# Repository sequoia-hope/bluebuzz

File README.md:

# bluebuzz-rm2

**Live project page & interactive schematic / PCB / 3D viewer:** <https://sequoia-hope.github.io/bluebuzz/> ([full-window board viewer](https://sequoia-hope.github.io/bluebuzz/viewer/), [renders & 3D gallery](https://sequoia-hope.github.io/bluebuzz/out/index.html))

A Bluetooth vibrator controller: RP2350A + Raspberry Pi Radio Module 2
(the first board, an nRF52840 module, is abandoned and kept in
`archive/nrf52840/`):
Wi-Fi 4 and Bluetooth 5.2 Classic + LE (CYW43439), so the toy can be a
Bluetooth **A2DP audio sink** (BTstack, in the Pico SDK) as well as a
BLE-controlled device, and a **USB audio device** (TinyUSB) over its USB-C.
**26 × 56.84 mm (`squish_pcb.dxf` with r = 10 mm lower tip offset inward by 2.0 mm), 6 layers.**
USB-C on the bottom tip is the only connector (the top dome is the RM2's RF keep-out);
every other lead is an SMT pad row on the back.

Sensing is a **4-sensor diamond array of Infineon DPS368 barometers on the back**
(North, East, West, South), meant to be cast in soft elastomer after Tenzer, Jentoft
& Howe, *The Feel of MEMS Barometers* (IEEE RAM 2014): rubber poured over
the array and vacuum degassed so it fills the pressure ports, after which
a load on the surface reads as pressure, linear to under 1 %, with 10 mN
resolution. Each sensor is on SPI1 with its own chip select (CSB low at
power-up selects SPI; the part has only two I2C addresses), on the
switched 3.3 V rail, 100n beside it. An **MP34DT05TR-A top-port digital PDM MEMS microphone** (`U40`) sits on the front upper-right shoulder (`PDM_CLK` on GPIO29, `PDM_DATA` on GPIO28), and an
**LSM6DS3TR-C IMU** on I2C1 sits on the back on the always-on rail,
with both interrupts on GPIOs for wake-on-motion.

Same pipeline as the parent (`python3 build.py` here; the `site` stage
rebuilds board `b` of the parent's `pcbview.toml`), with additions this
denser board forced: `route.py` hands freerouting a tamed DSN (GND
removed from its netlist since planes and pours carry it, the plane
layers marked unroutable, its fixed GND copper turned into keepouts),
lays the nets freerouting never closed by hand (the six QSPI lines, VBAT,
PG_N, the PWM and SWD hops, the USB climb, LX, WL_CS, the RP2350's lone
GND pin), draws every hand-laid bend at 45 degrees, and after routing
puts a via in every GND pad it can (cutting freerouting's wires from
under the ones it walled off; the finish stage re-closes them). The
stackup is six layers (GND / signal / VSYS pour / GND inside) because
four left 40-55 connections open. `ROUTE_DRY=1 python3 scripts/route.py`
lays only the locked pre-routes, for a quick DRC of them.

## What it is

| | |
|---|---|
| Host | RP2350A (QFN-60), Raspberry Pi's minimal design: 3.3 µH core buck, 12 MHz crystal (12 pF CL, 18 pF loads), W25Q32JVUUIQ 32 Mbit QSPI flash (3 x 4 USON), 27 R USB series, 10k/100n on RUN |
| Radio | RM2 (RMC20452T): gSPI with CS 25 as the Pico W, WL_ON on GPIO27, DATA on GPIO2 and CLK on GPIO3 (the board header overrides the SDK's defaults), DOUT via 470 R and nIRQ via 10 k into DATA. Vin from **VSYS** (3.0–4.8 V), VDDIO 3.3 V. Antenna end at the top board edge; the datasheet's RF keep-out is the top 5 mm of the board on every layer |
| Power | BQ24074 charger with power path (VBUS from the USB-C), TLV75533 3.3 V, TPS22918 switched sensor rail (GPIO4). /PGOOD → GPIO9 (the RP2350 has no VBUS detect) |
| Motors | two AO3400A low-side channels (GPIO13, GPIO17), 100 R gate / 100k pull-down, B5819W flybacks, 2 x 22 µF; pads VSYS M1 M2; 1 A per channel, fine for 3.7 V vibration motors |
| Touch | 4 x DPS368 on the back (SPI1: GPIO10 SCK, 11 SDI, 12 SDO; CS GPIO13-16), switched rail |
| Motion | LSM6DS3TR-C on I2C1 (GPIO6/7, 4.7k pull-ups), INT1/INT2 on GPIO5/18, CS high (I2C), SA0 low (0x6A), always on |
| UI | side button GPIO8, status LED GPIO22, charge LED on /CHG; battery 1M/1M into ADC0 = GPIO26 |
| USB | USB-C receptacle on the bottom edge, 5.1k on each CC, USBLC6-2P6 ESD, 27 R series at the chip |
| Pads (back, 1.6 x 2.2 mm at 2.0 mm) | top: **BAT** + - · bottom-left: **MOT** VSYS M1 M2 · under the radio: **SWD** SWDIO SWCLK RUN BOOT GND (pogo) |

## Programming

Bridge the **BOOT** pad to the **GND** pad beside it while applying
power (or call `reset_usb_boot()` from firmware) and the RP2350
enumerates as a UF2 drive on the USB-C. SWD on the same pad row for
debugging. Firmware: Pico SDK with `PICO_CYW43_SUPPORTED` and a board file
setting `CYW43_DEFAULT_PIN_WL_DATA_OUT/_IN/_HOST_WAKE = 2` and
`CYW43_DEFAULT_PIN_WL_CLOCK = 3`; BTstack's A2DP sink example is the
starting point for sound-to-vibration; the DPS368s through `spi1`, one
chip select at a time, in background mode at the rate the elastomer
response needs (the paper sampled at 100 Hz per sensor).

## Casting the array

Per the paper: a two-part room-temperature polyurethane (they used
VytaFlex 20, E ≈ 280 kPa) poured over the back of the board to 4-10 mm
over the sensors, then the mould placed in a vacuum chamber immediately
so the air trapped in the sensor ports is pulled out and the rubber
fills them; thinner rubber is more sensitive (1380 counts/N at 4 mm vs
165 at 10 mm for their sensor), thicker spreads the response. Solder the
BAT and MOT leads before casting; the SWD pads under the radio can stay
outside the cast area.

## Before ordering

- The **RM2 is not an LCSC part**: Raspberry Pi approved resellers; consign
  it at JLCPCB or solder it by hand (castellated, 1.5 mm pitch).
- The RM2 footprint was drawn from the datasheet's figure 6 (release 7,
  2026-02, `docs/RM2-datasheet.pdf`); check it against a module in hand.
- The DPS368 footprint is the LCSC/EasyEDA land for C3232508 (two
  columns of four 0.6 x 0.4 mm pads, 0.65 mm pitch, 1.45 mm apart);
  check it against Infineon's drawing. Pin 1 is the top-right pad.
- The DPS368 and the LSM6DS3TR-C are JLCPCB "extended" parts (a loading
  fee each per order). DPS368: $4.21 at 1-9, $3.60 at 10+ (2026-10).
- The flash is the 3 x 4 mm W25Q32JVUUIQ because the 2 x 3 mm 16 Mbit
  part had no stock; its KiCad land is by package name, check it against
  Winbond's drawing.
- No 3D models for the RM2 (not on LCSC) and the core inductor (LCSC
  land differs from KiCad's); the viewer draws boxes for them.

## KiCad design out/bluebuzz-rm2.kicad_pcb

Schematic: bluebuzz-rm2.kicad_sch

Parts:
C2, C13, C14, C15, C41, C43, C64, C82, C88, C89, C91, C92, C93, C94, C95, C96, C97, C98, C101, C102, C120, C121, C122, C123, C130, C132, C133, C140: 100n; C_0402_1005Metric
C10, C11, C12, C22, C52, C100, C131: 10u; C_0603_1608Metric
C20, C21, C51, C85: 1u; C_0603_1608Metric
C40, C42: 22u; C_0603_1608Metric
C50: 470p; C_0402_1005Metric
C80, C83: 4.7u; C_0402_1005Metric_small_pads
C81, C84: 4.7u; C_0402_1005Metric
C86, C87: 15p; C_0402_1005Metric
D1: CHG; LED_0603_1608Metric
D2: XL-1010RGBC; LED_1010_WS2812
D3, D4: B5819W; D_SOD-123
D5: BAT54C; SOT-23
D6: 1N4148WS; D_SOD-323
J1: USB-C; USB_C_Receptacle_HRO_TYPE-C-31-M-12
J2: BAT; PadRow_3x_solder
J3: SWD; PadRow_5x_pogo
J4: MOT; PadRow_3x_solder
J5: TP; PadRow_3x_pogo
J6: PROBE; JST_SH_BM03B-SRSS-TB_1x03-1MP_P1.00mm_Vertical; not fitted
L1: 3.3u; L_pol_2016
Q1, Q2: AO3400A; SOT-23
Q3: 2N7002; SOT-23
R1, R2: 5.1k; R_0402_1005Metric
R3, R4: 27R; R_0402_1005Metric
R10: 1.78k; R_0402_1005Metric
R11: 1.62k; R_0402_1005Metric
R12: 45.3k; R_0402_1005Metric
R13, R81, R88: 10k; R_0402_1005Metric
R14, R62: 330R; R_0402_1005Metric
R40, R42: 100R; R_0402_1005Metric
R41, R43, R130, R131: 4.7k; R_0402_1005Metric
R50, R63, R64, R66: 100k; R_0402_1005Metric
R60, R61: 1M; R_0402_1005Metric
R80: 470R; R_0402_1005Metric
R84: 33R; R_0402_1005Metric
R85: 10R; R_0402_1005Metric
R86, R87: 1k; R_0402_1005Metric
SW1: PWR; Panasonic_EVQPUL_EVQPUC
U1: RP2350A; QFN-60-1EP_7x7mm_P0.4mm_EP3.4x3.4mm_ThermalVias
U2: BQ24074RGT; VQFN-16-1EP_3x3mm_P0.5mm_EP1.6x1.6mm
U3: TLV75533PDBV; SOT-23-5
U5, U11: TPS22918DBVR; SOT-23-6
U6: W25Q32JVUUIQ; Winbond_USON-8-2EP_3x4mm_P0.8mm_EP0.2x0.8mm
U7: RM2
U10: USBLC6-2P6; SOT-666
U20, U21, U22, U23: DPS368; DPS368_LGA-8
U30: LSM6DS3TR-C; LGA-14_3x2.5mm_P0.5mm_LayoutBorder3x4y
U40: MP34DT05-A; MP34DT05_HCLGA-4
Y1: 12MHz; Crystal_SMD_3225-4Pin_3.2x2.5mm

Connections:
1V1: C80.1, C81.1, C82.1, C98.1, J5.3 (1V1), L1.1, U1.6 (DVDD), U1.23 (DVDD), U1.39 (DVDD), U1.50 (VREG_FB)
3V3A: C85.1, R85.2, U1.44 (ADC_AVDD)
3V3_SENS: C52.1, C120.1, C121.1, C122.1, C123.1, U5.5 (QOD), U5.6 (VOUT), U20.6 (VDDIO), U20.8 (VDD), U21.6 (VDDIO), U21.8 (VDD), U22.6 (VDDIO), U22.8 (VDD), U23.6 (VDDIO), U23.8 (VDD)
3V3_SYS: C21.1, C22.1, C51.1, C83.1, C88.1, C91.1, C92.1, C93.1, C94.1, C95.1, C96.1, C97.1, C102.1, C130.1, C131.1, C132.1, C140.1, J5.2 (3V3), R84.1, R85.1, R88.1, R130.1, R131.1, U1.1 (IOVDD), U1.11 (IOVDD), U1.20 (IOVDD), U1.30 (IOVDD), U1.38 (IOVDD), U1.45 (IOVDD), U1.49 (VREG_VIN), U1.53 (USB_OTP_VDD), U1.54 (IOVDD), U3.5 (OUT), U5.1 (VIN), U6.8 (VCC), U7.14 (VDDIO), U11.3 (ON), U30.5 (VDDIO), U30.8 (VDD), U30.12 (CS), U40.1 (VDD)
BOOTSEL: J3.4 (BOOT), R87.2
BTN: Q3.3 (D), U1.12 (GPIO8/BTN)
BTN_RAW: D5.1 (A1), Q3.1 (G), R64.1, SW1.2
CC1: J1.A5 (CC1), R1.1
CC2: J1.B5 (CC2), R2.1
CHG_LED: D1.1 (K), R14.1
CHG_N: R14.2, U2.9 (/CHG)
CT_SENS: C50.1, U5.4 (CT)
GND: C2.2, C10.2, C11.2, C12.2, C13.2, C14.2, C15.2, C20.2, C21.2, C22.2, C40.2, C41.2, C42.2, C43.2, C50.2, C51.2, C52.2, C64.2, C80.2, C81.2, C82.2, C83.2, C84.2, C85.2, C86.2, C87.2, C88.2, C89.2, C91.2, C92.2, C93.2, C94.2, C95.2, C96.2, C97.2, C98.2, C100.2, C101.2, C102.2, C120.2, C121.2, C122.2, C123.2, C130.2, C131.2, C132.2, C133.2, C140.2, D2.3 (GND), J1.A1 (GND), J1.A12 (GND), J1.B1 (GND), J1.B12 (GND), J1.S1 (SHIELD), J2.2 (-), J3.5 (GND), J6.2 (GND), J6.MP, Q1.2 (S), Q2.2 (S), Q3.2 (S), R1.2, R2.2, R10.2, R11.2, R12.2, R13.2, R41.2, R43.2, R50.2, R61.2, R63.2, R64.2, U1.47 (GND), U1.61 (GND), U2.4 (/CE), U2.6 (EN1), U2.8 (VSS), U2.17 (VSS), U3.2 (GND), U5.2 (GND), U6.4 (GND), U7.1 (GND), U7.4 (GND), U7.7 (GND), U7.11 (GND), U7.15 (GND), U7.21 (GND), U10.2 (GND), U11.2 (GND), U20.1 (GND), U20.7 (GND), U21.1 (GND), U21.7 (GND), U22.1 (GND), U22.7 (GND), U23.1 (GND), U23.7 (GND), U30.1 (SA0), U30.2 (SDx), U30.3 (SCx), U30.6 (GND), U30.7 (GND), U40.2 (LR), U40.5 (GND), Y1.2, Y1.4
ILIM: R11.1, U2.12 (ILIM)
IMU_INT1: U1.8 (GPIO5/IMU_INT1), U30.4 (INT1)
IMU_INT2: U1.29 (GPIO18/IMU_INT2), U30.9 (INT2)
ISET: R10.1, U2.16 (ISET)
LDO_EN: D5.3 (K), R63.1, R66.2, U3.3 (EN)
LED_DIN: D2.4 (DI), R62.2
LED_STAT: R62.1, U1.34 (GPIO22/LED)
LED_VDD: C133.1, D2.2 (VDD), U11.5 (QOD), U11.6 (VOUT)
MOTOR1_G: Q1.1 (G), R40.2, R41.1
MOTOR1_PWM: R40.1, U1.17 (GPIO13/M1_PWM)
MOTOR1_SW: D3.2 (A), J4.2 (M1), Q1.3 (D)
MOTOR2_G: Q2.1 (G), R42.2, R43.1
MOTOR2_PWM: R42.1, U1.28 (GPIO17/M2_PWM)
MOTOR2_SW: D4.2 (A), J4.3 (M2), Q2.3 (D)
PDM_CLK: U1.43 (GPIO29/PDM_CLK), U40.3 (CLK)
PDM_DATA: U1.42 (GPIO28/PDM_DATA), U40.4 (DOUT)
PG_N: U1.13 (GPIO9/PG), U2.7 (/PGOOD)
PWR_HOLD: D5.2 (A2), U1.31 (GPIO19/PWR_HOLD)
QSPI_SCLK: U1.56 (QSPI_SCLK), U6.6 (CLK)
QSPI_SD0: U1.57 (QSPI_SD0), U6.5 (DI/IO0)
QSPI_SD1: U1.59 (QSPI_SD1), U6.2 (DO/IO1)
QSPI_SD2: U1.58 (QSPI_SD2), U6.3 (/WP/IO2)
QSPI_SD3: U1.55 (QSPI_SD3), U6.7 (/HOLD/IO3)
QSPI_SS: R87.1, U1.60 (QSPI_SS), U6.1 (/CS)
RUN: C89.1, J3.3 (RUN), R88.2, U1.26 (RUN)
SCL: R131.2, U1.10 (GPIO7/SCL), U30.13 (SCL)
SDA: R130.2, U1.9 (GPIO6/SDA), U30.14 (SDA)
SENS_EN: R50.1, U1.7 (GPIO4/SENS_EN), U5.3 (ON)
SWCLK: J3.2 (SWCLK), J6.1 (SC), U1.24 (SWCLK)
SWDIO: J3.1 (SWDIO), J6.3 (SD), U1.25 (SWDIO)
TAC_CS1: U1.2 (GPIO0/TAC_CS1), U20.2 (CSB)
TAC_CS2: U1.18 (GPIO14/TAC_CS2), U21.2 (CSB)
TAC_CS3: U1.19 (GPIO15/TAC_CS3), U22.2 (CSB)
TAC_CS4: U1.27 (GPIO16/TAC_CS4), U23.2 (CSB)
TAC_SCK: U1.14 (GPIO10/TAC_SCK), U20.4 (SCK), U21.4 (SCK), U22.4 (SCK), U23.4 (SCK)
TAC_SDI: U1.15 (GPIO11/TAC_SDI), U20.3 (SDI), U21.3 (SDI), U22.3 (SDI), U23.3 (SDI)
TAC_SDO: U1.16 (GPIO12/TAC_SDO), U20.5 (SDO), U21.5 (SDO), U22.5 (SDO), U23.5 (SDO)
TMR: R12.1, U2.14 (TMR)
TS: J2.3 (T), R13.1, U2.1 (TS)
USB_DM: J1.A7 (D-), J1.B7 (D-), R4.1, U10.3 (IO2), U10.4 (IO2)
USB_DM_C: R4.2, U1.51 (USB_DM)
USB_DP: J1.A6 (D+), J1.B6 (D+), R3.1, U10.1 (IO1), U10.6 (IO1)
USB_DP_C: R3.2, U1.52 (USB_DP)
VBAT: C12.1, C15.1, J2.1 (+), R60.1, U2.2 (BAT), U2.3 (BAT)
VBAT_SENSE: C64.1, R60.2, R61.1, U1.40 (GPIO26/ADC0)
VBUS: C2.1, C10.1, C13.1, D6.2 (A), J1.A4 (VBUS), J1.A9 (VBUS), J1.B4 (VBUS), J1.B9 (VBUS), U2.13 (IN), U10.5 (VBUS)
VBUS_EN: D6.1 (K), R66.1
VREG_AVDD: C84.1, R84.2, U1.46 (VREG_AVDD)
VREG_LX: L1.2, U1.48 (VREG_LX)
VSYS: C11.1, C14.1, C20.1, C40.1, C41.1, C42.1, C43.1, C100.1, C101.1, D1.2 (A), D3.1 (K), D4.1 (K), J4.1 (VSYS), J5.1 (VSYS), SW1.1, U2.5 (EN2), U2.10 (OUT), U2.11 (OUT), U3.1 (IN), U7.16 (Vin), U11.1 (VIN)
WL_CLK: U1.5 (GPIO3/WL_CLK), U7.3 (SCLK)
WL_CS: U1.37 (GPIO25/WL_CS), U7.9 (CS)
WL_DATA: R80.2, R81.2, U1.4 (GPIO2/WL_DATA), U7.5 (DIN)
WL_DOUT: R80.1, U7.6 (DOUT)
WL_IRQ: R81.1, U7.10 (nIRQ)
WL_ON: U1.41 (GPIO27/WL_ON), U7.12 (WL_ON), U7.13 (WL_ON)
XIN: C86.1, U1.21 (XIN), Y1.1
XOUT: R86.1, U1.22 (XOUT)
XTAL2: C87.1, R86.2, Y1.3

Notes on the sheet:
bluebuzz-rm2 — generated schematic
109 components / 72 nets / 6-layer. Bluetooth-audio vibrator controller: RP2350A + Raspberry Pi RM2 (CYW43439); USB-C, every other lead on back-side pads; BQ24074 charger with power path, a soft power latch (button, GPIO hold, USB), two low-side motor channels, 4 DPS368 barometers on the back (four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
The one connector on the board, on the BOTTOM edge (the top edge is the
RM2's RF keep-out). A6/B6 and A7/B7 are tied or the board enumerates in
one cable orientation only; 5.1k on each CC. The USBLC6-2P6 clamps VBUS
and protects D+/D-; 27 R in each line at the RP2350 is the reference
design's.
1 — USB-C and ESD
EN2 = 1, EN1 = 0: the R_ILIM input limit (0.99 A). 45.3k = 6 h safety timer. ITERM open = 10% default. VSYS
is the power-path output and feeds the LDO, both motors AND the RM2 (Vin 3.0-4.8 V). /PGOOD goes to GPIO9:
the RP2350 has no VBUS detect of its own. J2: solder pads on the back for the cell: + - T. T is TS for a
cell with a 10 k NTC; fit it and leave R13 off. Without an NTC R13 holds TS mid-window (always charging).
2 — BQ24074 charger with power path
500 mA, 25 uA Iq. Feeds the RP2350, the flash, the sensors, the IMU
and the RM2's VDDIO; off (EN low) is the system's off state. The
motors and the RM2's Vin take VSYS directly.
4 — 3.3 V LDO, enabled by the power latch
1M/1M, 2.1 uA, into ADC0 (GPIO26). C64 feeds the ADC's
sampling charge; the RP2350's ADC input is 500 ohm-ish during
a sample, so oversample.
3 — battery voltage sense
Five 1.6 x 2.2 mm ENIG pads at 2.0 mm pitch for a
pogo clip: SWDIO SWCLK RUN BOOT GND. Bridge BOOT
to GND while applying power for the UF2
bootloader; SWD is for debugging only. J5: three
test pads (VSYS, 3V3, 1V1) for bring-up, GND on
the SWD row. J6: the Raspberry Pi Debug Probe's
3-pin JST-SH (1 SC, 2 GND, 3 SD), footprint only
(DNP), on the back.
6 — SWD / boot pads, test pads, debug-probe connector (back)
Press SW1: VSYS reaches the LDO's EN through D5 and 3V3 comes up; the
RP2350 boots and drives PWR_HOLD (GPIO19) high, so the board stays on
after release. Firmware reads the button on GPIO8 (Q3, active low,
internal pull-up) and switches off by driving PWR_HOLD low. R63 holds
EN off; R64 discharges the gate. USB in (VBUS through D6 and R66) also
holds EN on, so flashing and SWD need no button. Charging runs while
off. Status: a 1010 addressable RGB LED (WS2812B type) on GPIO22
through 330 R; its VSYS supply goes through U11 (a second TPS22918, ON
= 3V3_SYS), so it draws nothing while the system is off.
7 — power button (soft latch) and status LED

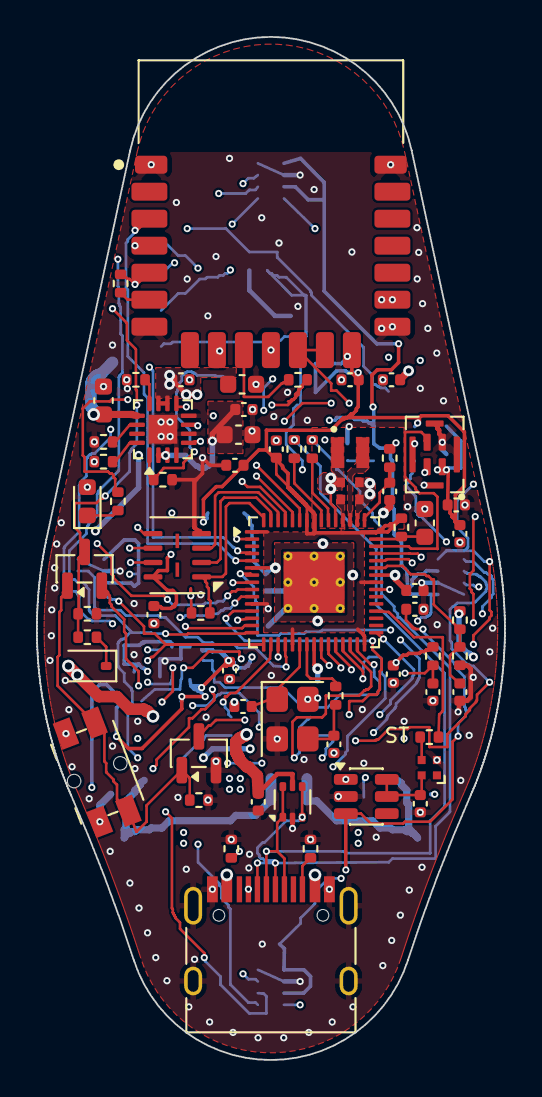
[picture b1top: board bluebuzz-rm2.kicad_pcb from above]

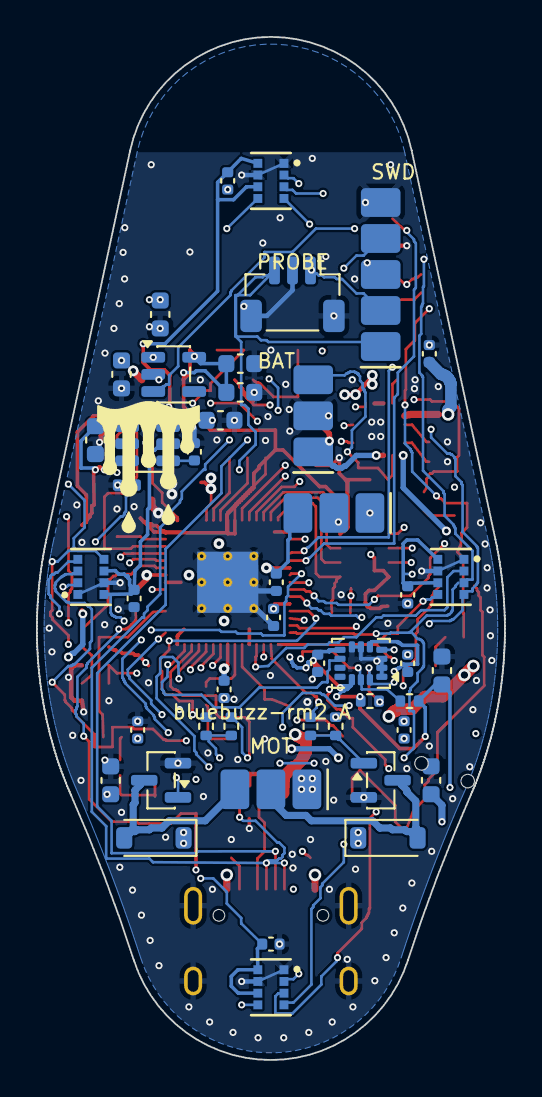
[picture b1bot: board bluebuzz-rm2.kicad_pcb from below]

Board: 6 copper layers, 26.0 x 56.8 mm, 109 parts (45 on the bottom side), 72 nets.

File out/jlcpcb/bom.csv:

Comment,Designator,Footprint,MPN,LCSC Part #
10u,"C10,C100,C11,C12,C131,C22,C52",C_0603_1608Metric,CL10A106KP8NNNC,C19702
100n,"C101,C102,C120,C121,C122,C123,C13,C130,C132,C133,C14,C140,C15,C2,C41,C43,C64,C82,C88,C89,C91,C92,C93,C94,C95,C96,C97,C98",C_0402_1005Metric,CL05B104KO5NNNC,C1525
22u,"C40,C42",C_0603_1608Metric,CL10A226MP8NUNE,C86295
470p,C50,C_0402_1005Metric,0402CG471J500NT,C75274
4.7u,"C80,C83",C_0402_1005Metric_small_pads,CL05A475MP5NRNC,C23733
4.7u,"C81,C84",C_0402_1005Metric,CL05A475MP5NRNC,C23733
1u,"C20,C21,C51,C85",C_0603_1608Metric,CL10A105KB8NNNC,C15849
15p,"C86,C87",C_0402_1005Metric,0402CG150J500NT,C1548
CHG,D1,LED_0603_1608Metric,19-217/GHC-YR1S2/6T,C2986059
XL-1010RGBC,D2,LED_1010_WS2812,XL-1010RGBC-2812B-S,C51900942
B5819W,"D3,D4",D_SOD-123,B5819W,C8598
BAT54C,D5,SOT-23,"BAT54C,215",C37704
1N4148WS,D6,D_SOD-323,1N4148WS,C2128
USB-C,J1,USB_C_Receptacle_HRO_TYPE-C-31-M-12,TYPE-C-31-M-12,C165948
3.3u,L1,L_pol_2016,AOTA-B201610S3R3-101-T,C42411119
AO3400A,"Q1,Q2",SOT-23,AO3400A,C20917
2N7002,Q3,SOT-23,2N7002,C8545
1.78k,R10,R_0402_1005Metric,0402WGF1781TCE,C113478
1.62k,R11,R_0402_1005Metric,0402WGF1621TCE,C61897
45.3k,R12,R_0402_1005Metric,0402WGF4532TCE,C26980
10k,"R13,R81,R88",R_0402_1005Metric,0402WGF1002TCE,C25744
330R,"R14,R62",R_0402_1005Metric,0402WGF3300TCE,C25104
5.1k,"R1,R2",R_0402_1005Metric,0402WGF5101TCE,C25905
27R,"R3,R4",R_0402_1005Metric,0402WGF270JTCE,C25100
100R,"R40,R42",R_0402_1005Metric,0402WGF1000TCE,C25076
4.7k,"R130,R131,R41,R43",R_0402_1005Metric,0402WGF4701TCE,C25900
1M,"R60,R61",R_0402_1005Metric,0402WGF1004TCE,C26083
100k,"R50,R63,R64,R66",R_0402_1005Metric,0402WGF1003TCE,C25741
470R,R80,R_0402_1005Metric,0402WGF4700TCE,C25117
33R,R84,R_0402_1005Metric,0402WGF330JTCE,C25105
10R,R85,R_0402_1005Metric,0402WGF100JTCE,C25077
1k,"R86,R87",R_0402_1005Metric,0402WGF1001TCE,C11702
PWR,SW1,Panasonic_EVQPUL_EVQPUC,EVQPUC02K,C79174
RP2350A,U1,QFN-60-1EP_7x7mm_P0.4mm_EP3.4x3.4mm_ThermalVias,RP2350A,C42411118
USBLC6-2P6,U10,SOT-666,USBLC6-2P6,C15999
TPS22918DBVR,"U11,U5",SOT-23-6,TPS22918DBVR,C131941
BQ24074RGT,U2,VQFN-16-1EP_3x3mm_P0.5mm_EP1.6x1.6mm,BQ24074RGTR,C54313
DPS368,"U20,U21,U22,U23",DPS368_LGA-8,DPS368XTSA1,C3232508
TLV75533PDBV,U3,SOT-23-5,TLV75533PDBVR,C404027
LSM6DS3TR-C,U30,LGA-14_3x2.5mm_P0.5mm_LayoutBorder3x4y,LSM6DS3TR-C,C967633
MP34DT05-A,U40,MP34DT05_HCLGA-4,MP34DT05TR-A,C2688664
W25Q32JVUUIQ,U6,Winbond_USON-8-2EP_3x4mm_P0.8mm_EP0.2x0.8mm,W25Q32JVUUIQ,C2999380
12MHz,Y1,Crystal_SMD_3225-4Pin_3.2x2.5mm,ABM8-272-T3,C20625731

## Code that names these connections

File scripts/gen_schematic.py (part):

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        R = list(sides.get("r", []))
        T = list(sides.get("t", []))
        B = list(sides.get("b", []))
        # Top/bottom pin names run vertically INSIDE the box and would be
        # written straight through any side-pin name whose text reaches the
        # same columns. Where they would collide, reserve as many side slots
        # as the vertical name is tall so the two never share a row.
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            ys = [p[1] for p in pts]
            if max(ys) - min(ys) >= max(xs) - min(xs):
                # pins stack vertically -> park the text alongside the body,
                # between the two pins so it cannot reach either run
                rx, ry, rj = x + hw + 0.6, y - 2.0, "left bottom"
                vx, vy, vj = x + hw + 0.6, y + 1.1, "left bottom"
            else:
                # pins run left-right -> stack the text above and below,
                # stepped off the pin axis so it clears the wires' corners
                rx, ry, rj = x + 1.9, y - hh - 2.8, "left bottom"
                vx, vy, vj = x + 1.9, y + hh + 4.2, "left bottom"
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    def label(self, net, p, rot=0, just="left", size=1.0, flag=2.54, keep=False):
        """Name a wire that KiCad would otherwise auto-name.

        These are GLOBAL labels even though the run is local, because a
        plain label on the root sheet comes back out of the netlister as
        `/LED_D7`, and the board is matched to circuit.py by net name — a
        rename would relabel every net on a hand-routed board. Drawn small
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            ("48", "VREG_LX"), None, None, None, None,
            ("46", "VREG_AVDD"), None, None, None, None, ("44", "ADC_AVDD")]
    right = [gpio(13, "M1_PWM"), gpio(17, "M2_PWM"), None,
             gpio(2, "WL_DATA"), gpio(3, "WL_CLK"), gpio(27, "WL_ON"), gpio(25, "WL_CS"), None,
             gpio(10, "TAC_SCK"), gpio(11, "TAC_SDI"), gpio(12, "TAC_SDO"), None,
             gpio(0, "TAC_CS1"), gpio(14, "TAC_CS2"), gpio(15, "TAC_CS3"), gpio(16, "TAC_CS4"), None,
             gpio(29, "PDM_CLK"), gpio(28, "PDM_DATA"), None,
             gpio(6, "SDA"), gpio(7, "SCL"), gpio(5, "IMU_INT1"), gpio(18, "IMU_INT2"), None,
             gpio(19, "PWR_HOLD"),
             gpio(4, "SENS_EN"), gpio(22, "LED"), gpio(8, "BTN"), gpio(9, "PG"), None,
             gpio(26, "ADC0")]
    top = [("1", "IOVDD", ["11", "20", "30", "38", "45", "54"]), ("49", "VREG_VIN"),
           ("53", "USB_OTP_VDD"), None, ("6", "DVDD", ["23", "39"]), ("50", "VREG_FB")]
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    "radio": {"l": [("3", "SCLK"), None, ("5", "DIN"), None, None, None, ("6", "DOUT"),
                    None, None, None, ("10", "nIRQ"), None, None, None, ("9", "CS"), None,
                    ("12", "WL_ON", ["13"])],
              "r": [("8", "GPIO0"), ("18", "GPIO1"), ("17", "GPIO2"), None,
                    ("2", "NC"), ("19", "NC"), ("20", "NC")],
              "t": [("16", "Vin"), None, None, ("14", "VDDIO")],
              "b": [("1", "GND", ["4", "7", "11", "15", "21"])]},
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    s.rail("VBUS", (u["13"][0] - 7.62, u["13"][1]))
    # /CE and EN1 to ground, EN2 to VSYS (ILIM mode, also while the system is off):
    # a short stub left, then a symbol standing the right way up
    for pin, rail, dx in (("4", "GND", 7.62), ("5", "VSYS", 15.24), ("6", "GND", 7.62)):
        bk.take("U2", pin, rail)
        e = (u[pin][0] - dx, u[pin][1])
        s.wire(u[pin], e)
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    s.rail("VBAT", (xb, u["2"][1] - 8.89))
    bk.take("U2", "7", "PG_N")
    s.wire(u["7"], (u["7"][0] + 10.16, u["7"][1]))
    s.glabel("PG_N", (u["7"][0] + 10.16, u["7"][1]))
    bk.take("U2", "9", "CHG_N")
    ych = u["9"][1]
    xled = u["9"][0] + 33.02
    s.wire(u["9"], (xled, ych))
    s.label("CHG_N", (u["9"][0] + 5.08, ych), size=1.0)
    r14 = put(s, cir, "R14", xled, ych - 3.81)
    bk.take("R14", "2", "CHG_N")
    bk.take("R14", "1", "CHG_LED")
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    bk.take("D1", "1", "CHG_LED")
    bk.take("D1", "2", "VSYS")
    s.wire(r14["1"], d1["1"])
    s.label("CHG_LED", (xled, q((r14["1"][1] + d1["1"][1]) / 2.0)), size=1.0)
    s.wire(d1["2"], (d1["2"][0], d1["2"][1] - 3.81))
    s.rail("VSYS", (d1["2"][0], d1["2"][1] - 3.81))
    ybot = u["16"][1]
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    s.note("EN2 = 1, EN1 = 0: the R_ILIM input limit (0.99 A). 45.3k = 6 h "
           "safety timer. ITERM open = 10% default. VSYS is the power-path "
           "output and feeds the LDO, both motors AND the RM2 (Vin 3.0-4.8 V). "
           "/PGOOD goes to GPIO9: the RP2350 has no VBUS detect of its own. "
           "J2: solder pads on the back for the cell: + - T. T is TS for a "
           "cell with a 10 k NTC; fit it and leave R13 off. Without an NTC "
           "R13 holds TS mid-window (always charging).",
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    s.wire((xin, u["1"][1]), (xin, u["1"][1] - 6.35))
    s.rail("VSYS", (xin, u["1"][1] - 6.35))
    s.wire(u["3"], (u["3"][0] - 17.78, u["3"][1]))
    s.glabel("LDO_EN", (u["3"][0] - 17.78, u["3"][1]), just="right")
    bk.take("U3", "5", "3V3_SYS")
    s.wire(u["5"], (u["5"][0] + 10.16, u["5"][1]))
    s.wire((u["5"][0] + 10.16, u["5"][1]), (u["5"][0] + 10.16, u["5"][1] - 6.35))
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    bk.take("C64", "1", "VBAT_SENSE")
    s.junction((x + 12.7, ymid))
    s.wire((x + 12.7, ymid), (x + 25.4, ymid))
    s.glabel("VBAT_SENSE", (x + 25.4, ymid))
    s.note("1M/1M, 2.1 uA, into ADC0 (GPIO26). C64 feeds the ADC's sampling "
           "charge; the RP2350's ADC input is 500 ohm-ish during a sample, so "
           "oversample.", x - 8.0, r61["2"][1] + 12.7, 96.0)
    s.end()
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    m1 = motor_channel(s, cir, bk, 1, x, y + 20.32)
    m2 = motor_channel(s, cir, bk, 2, x, y + 60.96)
    # pads_3: pin 2 (M1) is the middle slot of five, so the box centres on
    # channel 1's drain run; pin 3 (M2) is two rows below it
    j4 = put(s, cir, "J4", m1[0] + 40.64, m1[1], hide_value=True)
    assert abs(j4["2"][1] - m1[1]) < 0.01, "J4 pin 2 must sit on channel 1's drain run"
    bk.take("J4", "2", "MOTOR1_SW")
    bk.take("J4", "3", "MOTOR2_SW")
    bk.take("J4", "1", "VSYS")
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    s.wire(j4["1"], (j4["1"][0] - 6.35, j4["1"][1]))
    s.rail("VSYS", (j4["1"][0] - 6.35, j4["1"][1]), rot=90)
    bank(s, cir, bk, ["C40", "C41", "C42", "C43"], x + 5.08, y + 93.98, "VSYS")
    s.note("Two identical PWM channels (GPIO13, GPIO17): AO3400A low side, "
           "B5819W 1 A Schottky across each motor, 2 x 22 u of bulk at the "
           "pads. R41/R43 hold the gates down until firmware runs. J4 is three "
           "solder pads on the back: VSYS M1 M2 -- the two motors share the "
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    s.rail("3V3_SYS", (u5["1"][0] - 8.89, u5["1"][1]))
    bk.take("U5", "3", "SENS_EN")
    s.wire(u5["3"], (u5["3"][0] - 25.4, u5["3"][1]))
    s.glabel("SENS_EN", (u5["3"][0] - 25.4, u5["3"][1]), just="right")
    xpd = u5["3"][0] - 17.78
    s.junction((xpd, u5["3"][1]))
    vdrop(s, cir, bk, "R50", xpd, u5["3"][1], ref_off=(-6.9, 0.0))
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    s.rail("GND", (u5["2"][0], u5["2"][1] + 5.08))
    bk.take("U5", "4", "CT_SENS")
    s.wire(u5["4"], (u5["4"][0] - 8.89, u5["4"][1]))
    s.label("CT_SENS", (u5["4"][0] - 7.4, u5["4"][1]), size=1.0)
    c50 = put(s, cir, "C50", u5["4"][0] - 8.89, u5["4"][1] + 3.81, ref_off=(-4.5, -2.0))
    bk.take("C50", "1", "CT_SENS")
    bk.take("C50", "2", "GND")
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    for k, (ref, cap) in enumerate(TACTILE, 1):
        r, c = divmod(k - 1, TACTILE_COLS)
        u = put(s, cir, ref, x + c * 66.04, y + r * 66.04, hide_value=True, ref_off="corner")
        for pin, net in (("2", f"TAC_CS{k}"), ("4", "TAC_SCK"), ("3", "TAC_SDI"), ("5", "TAC_SDO")):
            bk.take(ref, pin, net)
            s.wire(u[pin], (u[pin][0] - 10.16, u[pin][1]))
            s.glabel(net, (u[pin][0] - 10.16, u[pin][1]), just="right")
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           "2014 (The Feel of MEMS Barometers): rubber poured over the array "
           "and pressure-cast (not vacuum: DPS368 p.43) so it fills the ports; a load on the "
           "surface then reads as pressure. CSB low at power-up puts each "
           "sensor in SPI mode; SPI1 on GPIO10-12, one chip select each on "
           "GPIO0 and GPIO14-16. 100n at every sensor.",
           x - 20.0, y + 66.04 + 30.48, 150.0)
    s.end()

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def blk_mic(s, cir, bk, x, y):
    s.begin("14 — PDM MEMS microphone: MP34DT05-A (top-port)")
    u = put(s, cir, "U40", x, y, ref_off="corner")
    for pin, net in (("3", "PDM_CLK"), ("4", "PDM_DATA")):
        bk.take("U40", pin, net)
        s.wire(u[pin], (u[pin][0] - 15.24, u[pin][1]))
        s.glabel(net, (u[pin][0] - 15.24, u[pin][1]), just="right")
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    s.rail("GND", (u["5"][0], yb + 3.81))
    s.note("ST MP34DT05TR-A top-port digital PDM MEMS microphone (3 x 4 x 1 mm "
           "HCLGA-4, 64 dB SNR, 122.5 dBSPL AOP) on the always-on 3.3 V rail. "
           "LR tied to GND selects the left-channel slot; CLK on GPIO29, DOUT "
           "on GPIO28 (PIO PDM state machine). Top acoustic port needs no PCB hole.",
           x - 20.0, y + 30.48, 130.0)
    s.end()

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            yb = r["1"][1] + 2.54
            s.path(r["1"], (xp, yb), (xp - 5.08, yb), (xp - 5.08, r["1"][1] - 1.27))
            s.rail("3V3_SYS", (xp - 5.08, r["1"][1] - 1.27))
    for pin, net in (("4", "IMU_INT1"), ("9", "IMU_INT2")):
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
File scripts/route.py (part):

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    length = [sum(math.hypot(b[0] - a[0], b[1] - a[1]) for a, b, _ in g[1])
              for g in mov]
    blocked = [{ly for ly in LAYERS if wg.blocked(g, ly)} for g in mov]
    # A run that lands on an SMD pad of its own net is pinned to that pad's
    # layer: moved, it ends in mid-air over the pad. J6's GND hop on the
    # back was moved to In2 this way and left a dangling locked wire across
    # the In2 corridor by the USB resistors (2026-10-18).
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        rt.via((ex + dx, ey + dy), "GND")

    # ---- pre-route: the charger's power pins ----
    # The pin pairs first (VBAT 2+3, VSYS 10+11: 0.25 wide at 0.5 pitch, a
    # bridge inside the row touches nothing else).
    u2 = fps["U2"]
    assert abs(u2.GetOrientationDegrees() - 90) < 0.01, "route.py lays the charger's power copper for U2 at rot 90"
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    for a, b in ((2, 3), (10, 11)):
        rt.track(P2[a], P2[b], pad_of(u2, a).GetNetname(), width=0.25)

    # EN2 (pin 5, VSYS): a lone plane-net pad in a 0.5 mm QFN row --
    # freerouting left it with a 0.7 mm stub and no via, twice. Stub
    # outward from the pad, a via into the In3 plane at the end, locked.
    u2x, u2y = rel(u2.GetPosition())
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    rt.path([p5, (p5[0] + 0.25, p5[1]), (p5[0] + 0.33, out[1]), out], "VSYS", width=0.15, chamfer=0.0)
    rt.via(out, "VSYS")

    # OUT (pins 10+11 -> the In3 VSYS plane), 2 A when both motors run at
    # their 1 A rating (check_current.py): an F.Cu VSYS zone over the pin
    # row's outer end, taking in C14's VSYS pad and reaching east to the
    # OUT cap C11 (which cannot take a via: the cell pad is under it on the
    # back), with four 0.6/0.3 vias (0.8 A each, stackup.md): two in C14's
    # pad, two east of pin 9 (CHG_N keeps its exit below them, toward pin
    # 8). Nothing can go straight above the pins: C120, the top-left
    # sensor's cap, is under them on the back. It replaces one 0.2 via
    # (0.53 A, the phase-7 review's B2).
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                priority=2, name="pwr_vsys_out", full=True)
    z.SetLocked(True)

    # CHG_N (pin 9) sits between the OUT pins and the OUT copper's vias:
    # out of the pad's inner end, east to a via between the vias and pin 8
    # (freerouting left it open in 5 of 8 orderings without it).
    p9in = (P2[9][0], P2[9][1] + 0.19)
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            rt.via((vx, vy), "VBAT", drill=0.25, size=0.5)
    c15 = pad_net(fps["C15"], "VBAT").GetBoundingBox()
    c12 = pad_net(fps["C12"], "VBAT").GetBoundingBox()
    bx0 = jx0 - 0.05                               # east of U2's right pins (-4.12), EN2 (-3.91), PG_N (-4.06)
    bx1 = max(jx0 + 1.40, to_mm(c15.GetRight()) - CX + 0.15, to_mm(c12.GetRight()) - CX + 0.15)
    by0 = min(y_hi - 0.3, to_mm(c15.GetTop()) - CY - 0.15)
    by1 = y_hi + 0.65                              # 5.15: clears C91 (y>=5.49)
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    c10v = rel(pad_net(fps["C10"], "VBUS").GetPosition())
    p13_u2 = rel(pad_of(fps["U2"], 13).GetPosition())
    rt.path([c10v, (p13_u2[0] - 0.3, c10v[1]), p13_u2], "VBUS", width=0.4, chamfer=0.0)
    # TMR (pin 14 -> R12) and ISET (pin 16 -> R10) on F.Cu before vias land in front of pins 14/16
    p14_u2 = rel(pad_of(fps["U2"], 14).GetPosition())
    r12_t = rel(pad_net(fps["R12"], "TMR").GetPosition())
    rt.path([p14_u2, (p14_u2[0] - 0.40, p14_u2[1]), (r12_t[0] + 0.15, r12_t[1]), r12_t], "TMR", width=0.15, chamfer=0.0)
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        rt.track((px, py), v, pad.GetNetname(), width=0.2)


    # ---- pre-route: PG_N, charger pin 7 -> GPIO9 (pin 13) ----
    pg = rel(pad_of(fps["U2"], 7).GetPosition())
    g13 = rel(pad_of(fps["U1"], 13).GetPosition())
    v1_pg = (pg[0] + 0.50, pg[1] + 0.05)
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    rt.via(v2_pg, "PG_N")
    rt.track(v2_pg, g13, "PG_N", width=0.15)

    # ---- pre-route: BTN (pin 12) out of the channel ----
    p12 = rel(pad_of(fps["U1"], 12).GetPosition())
    v12 = (p12[0] - 1.45, p12[1] + 0.4)
    rt.path([p12, (p12[0] - 1.05, p12[1]), v12], "BTN", width=0.15)
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    for rref, net in (("R3", "USB_DP"), ("R4", "USB_DM")):
        rt.via(rel(pad_net(fps[rref], net).GetPosition()), net)

    # ---- pre-route: escapes for WL_CS (pin 37), WL_CLK (pin 5), SENS_EN, IMU_INT1 (pins 7, 8), SWCLK, SWDIO (24, 25) ----
    p37 = rel(pad_of(fps["U1"], 37).GetPosition())
    v37 = (p37[0] + 0.75, p37[1])
    rt.via(v37, "WL_CS")
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    v24 = (p24[0] + 0.44, p24[1] + 1.17)     # east of the 1V1 spoke via below pin 23
    rt.path([p24, (p24[0], p24[1] + 0.73), v24], "SWCLK", width=0.15, chamfer=0.0)
    rt.via(v24, "SWCLK")
    # TAC_CS1 (pin 2): west to a via in the lane.
    p2u = rel(pad_of(fps["U1"], 2).GetPosition())
    v2u = (p2u[0] - 0.85, p2u[1])
    rt.track(p2u, v2u, "TAC_CS1", width=0.15)
    rt.via(v2u, "TAC_CS1")
    # TAC_CS2 (pin 18) and TAC_CS3 (pin 19): south escape vias so they leave on In2/B.Cu without crossing XIN/XOUT
    p18u = rel(pad_of(fps["U1"], 18).GetPosition())
    v18u = (p18u[0], p18u[1] + 0.70)
    rt.track(p18u, v18u, "TAC_CS2", width=0.15)
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    v19u = (p19u[0] + 0.05, p19u[1] + 1.25)
    rt.path([p19u, (p19u[0], p19u[1] + 0.65), (v19u[0], p19u[1] + 0.70), v19u], "TAC_CS3", width=0.15, chamfer=0.0)
    rt.via(v19u, "TAC_CS3")
    # XIN (pin 21 -> Y1.1 -> C86) and XOUT (pin 22 -> R86.1) and XTAL2 (R86.2 -> C87.1 -> Y1.3) on F.Cu
    p21u = rel(pad_of(fps["U1"], 21).GetPosition())
    y1_xin = rel(pad_net(fps["Y1"], "XIN").GetPosition())
    c86_xin = rel(pad_net(fps["C86"], "XIN").GetPosition())
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    c50_ct = rel(pad_net(fps["C50"], "CT_SENS").GetPosition())
    u5_ct = rel(pad_net(fps["U5"], "CT_SENS").GetPosition())
    rt.path([c50_ct, (c50_ct[0] + abs(u5_ct[1] - c50_ct[1]), u5_ct[1]), u5_ct], "CT_SENS", layer=pcbnew.B_Cu, width=0.15, chamfer=0.0)
    # pins 25-29 (SWDIO, RUN, TAC_CS4, MOTOR2_PWM, IMU_INT2) as one staircase:
    fan = ((25, "SWDIO", 0.53, 0.69, (0.0, 0.08)), (26, "RUN", 0.41, 0.87, (0.0, 0.13)),
           (27, "TAC_CS4", 0.37, 1.11, (0.0, 0.43)), (28, "MOTOR2_PWM", 0.37, 1.17, (0.0, 0.79)),
           (29, "IMU_INT2", 0.37, 0.75, (0.18, 0.0)))
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    p45u = rel(pad_of(fps["U1"], 45).GetPosition())
    r85_s = rel(pad_net(fps["R85"], "3V3_SYS").GetPosition())
    rt.path([p45u, (r85_s[0] - abs(p45u[1] - r85_s[1]), p45u[1]), r85_s], "3V3_SYS", width=0.20, chamfer=0.0)
    # Right-side parallel escapes for PDM_CLK (pin 43), PDM_DATA (pin 42), WL_ON (pin 41), and VBAT_SENSE (pin 40)
    p43u = rel(pad_of(fps["U1"], 43).GetPosition())
    p43_esc = (9.25, 10.45)
    rt.path([p43u, (7.65, 10.30), (7.78, 10.43), (9.23, 10.43), p43_esc], "PDM_CLK", width=0.15, chamfer=0.0)
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    p40u = rel(pad_of(fps["U1"], 40).GetPosition())
    p40_esc = (7.48, 11.55)
    rt.path([p40u, (6.35, 11.50), (6.46, 11.39), (7.32, 11.39), p40_esc], "VBAT_SENSE", width=0.15, chamfer=0.0)
    # Left-side escapes for TAC_SCK (pin 14), TAC_SDI (pin 15), and U22's inter-column B.Cu lanes
    p14u = rel(pad_of(fps["U1"], 14).GetPosition())
    p14_esc = (-1.95, 14.85)
    rt.path([p14u, (-1.45, 14.70), (-1.60, 14.85), p14_esc], "TAC_SCK", width=0.15, chamfer=0.0)
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        nv = preroute(board, design, "WL_IRQ", (r81i, [pcbnew.F_Cu]), (u710, [pcbnew.F_Cu]))
    print(f"WL_IRQ: {'no path' if nv is None else f'{nv} vias'}")

    # WL_DATA (gSPI data, R81 -> pin 4 and U7.5 -> R81) first so WL_CS/WL_CLK don't wall off R81 or pin 4
    r81 = rel(pad_net(fps["R81"], "WL_DATA").GetPosition())
    p4 = rel(pad_of(fps["U1"], 4).GetPosition())
    nv = preroute(board, design, "WL_DATA", (r81, [pcbnew.F_Cu]), (p4, [pcbnew.F_Cu]),
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        nv = preroute(board, design, "VBAT_SENSE", (p40_esc, [pcbnew.F_Cu]), (r60_vs, [pcbnew.F_Cu]))
    print(f"VBAT_SENSE: {'no path' if nv is None else f'{nv} vias'}")

    # TAC_CS2 (pin 18's escape via -> the East sensor U21) and TAC_CS3 (pin 19's escape via -> the West sensor U22)
    u21 = rel(pad_net(fps["U21"], "TAC_CS2").GetPosition())
    nv = preroute(board, design, "TAC_CS2", (v18u, [pcbnew.In2_Cu, pcbnew.B_Cu]), (u21, [pcbnew.B_Cu]),
                  layers=[pcbnew.In2_Cu, pcbnew.B_Cu], avoid=[(pcbnew.B_Cu, 9.5, 10.8, 10.4, 12.1)])
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    j2_ts = rel(pad_net(fps["J2"], "TS").GetPosition())
    nv = preroute(board, design, "TS", (r13, [pcbnew.F_Cu]), (j2_ts, [pcbnew.B_Cu]))
    print(f"TS: {'no path' if nv is None else f'{nv} vias'}")
    # TAC_CS1 (pin 2's escape via -> the North sensor U20)
    u20 = rel(pad_net(fps["U20"], "TAC_CS1").GetPosition())
    cols = sorted({round(rel(pd.GetPosition())[0], 2) for pd in fps["U20"].Pads()})
    ys = [rel(pd.GetPosition())[1] for pd in fps["U20"].Pads()]
    gap = (pcbnew.B_Cu, cols[0] + 0.3, min(ys) - 0.6, cols[-1] - 0.3, max(ys) + 0.6)
    nv = preroute(board, design, "TAC_CS1", (v2u, every), (u20, [pcbnew.B_Cu]), avoid=[gap])
    print(f"TAC_CS1: {'no path' if nv is None else f'{nv} vias'}")
    # IMU_INT1 (pin 8's escape via -> the IMU, U30 on B.Cu), IMU_INT2 (fan_vias["IMU_INT2"] -> U30.9), SCL (v10u -> U30 -> R131), SDA (v9u -> U30 -> R130)
    p30 = rel(pad_net(fps["U30"], "IMU_INT1").GetPosition())
    nv = preroute(board, design, "IMU_INT1", (v8, every), (p30, [pcbnew.B_Cu]))
    print(f"IMU_INT1: {'no path' if nv is None else f'{nv} vias'}")
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
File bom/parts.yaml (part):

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    buck) on 6, 23, 39 and VREG_FB 50; VREG_VIN 49 and USB_OTP_VDD 53 on
    3.3 V; ADC_AVDD 44 through 10 R; VREG_AVDD 46 through 33 R; VREG_PGND
    47 to GND; VREG_LX 48 to the 3.3 uH. XIN 21 / XOUT 22, SWCLK 24 /
    SWDIO 25 / RUN 26, USB_DM 51 / USB_DP 52, QSPI 55..60. GPIO0..25 on
    2,3,4,5,7,8,9,10,12..19,27,28,29,31..37; GPIO26..29 (ADC0..3) on 40..43.
    The core regulator, decoupling and USB series resistors follow
    Raspberry Pi's RP2350A minimal design (RP-006440).

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    and LE, PA/LNA, PCB antenna, RF shield, modular FCC/IC/CE. Vin 3.0-4.8 V
    (RF degrades below 3.2 V) -- fed from VSYS here; VDDIO 3.3 V. TX 271 mA
    peak, RX 43 mA, power-save ~1.2 mA. gSPI to the RP2350's PIO: pin 3
    SCLK <- GPIO29, pin 5 DIN <- GPIO24, pin 6 DOUT -> GPIO24 through 470 R,
    pin 10 nIRQ -> GPIO24 through 10 k, pin 9 CS <- GPIO25, pins 12+13
    WL_ON/BT_ON <- GPIO23 (the Pico W defaults). Pins 8/17/18 are the
    module's own GPIO0/2/1, left open. RF keep-out per fig. 6: no metal
    within the top 5.0 mm of the body, 10.5 mm either side, 13.5 mm beyond.
    Only works with Raspberry Pi microcontrollers (bespoke firmware loaded
    by the Pico SDK over gSPI; BTstack for Bluetooth).
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  notes: >
    1.5 A linear charger with power path (bike-tracker, SLUS810). VSYS, the
    power-path output, feeds the LDO, the motors AND the RM2. /PGOOD to
    GPIO9: the RP2350 has no VBUS detect of its own.

ldo:
  mpn: TLV75533PDBVR
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  verified: api
  notes: >
    ST 6-axis IMU, LGA-14 2.5 x 3 mm, on I2C1 (CS tied high, SA0 to GND:
    address 0x6A) with INT1/INT2 to GPIO17/18, on the always-on 3.3 V so
    it can wake the system on motion.
baro:
  mpn: DPS368XTSA1
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  lcsc: C37704
  footprint: Package_TO_SOT_SMD:SOT-23
  verified: api          # 30 V 200 mA common-cathode pair, 295k in stock 2026-10-18
  notes: "Power latch: the button and PWR_HOLD OR'd onto the LDO's EN (pin 1 A1, 2 A2, 3 K)."
signal_diode:
  mpn: 1N4148WS
  lcsc: C2128
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  lcsc: C8545
  footprint: Package_TO_SOT_SMD:SOT-23
  verified: api          # basic part, 2.6M in stock 2026-10-18
  notes: "Reads the power button (gate on BTN_RAW, up to 4.4 V) onto GPIO8 (pin 1 G, 2 S, 3 D)."
motor_fet:
  mpn: AO3400A
  lcsc: C20917
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  notes: >
    Status LED (user: a 1010 addressable LED). Fed from VSYS, switched so it
    is unpowered when the system is off (its 0.35 mA idle current would
    otherwise drain the cell): through U11 (TPS22918, ON = 3V3_SYS); DI from GPIO5 through 330 R. Pins: 1 DOUT,
    2 VDD, 3 GND, 4 DI (EasyEDA C51900942).
debug_jst:
  mpn: BM03B-SRSS-TB(LF)(SN)
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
